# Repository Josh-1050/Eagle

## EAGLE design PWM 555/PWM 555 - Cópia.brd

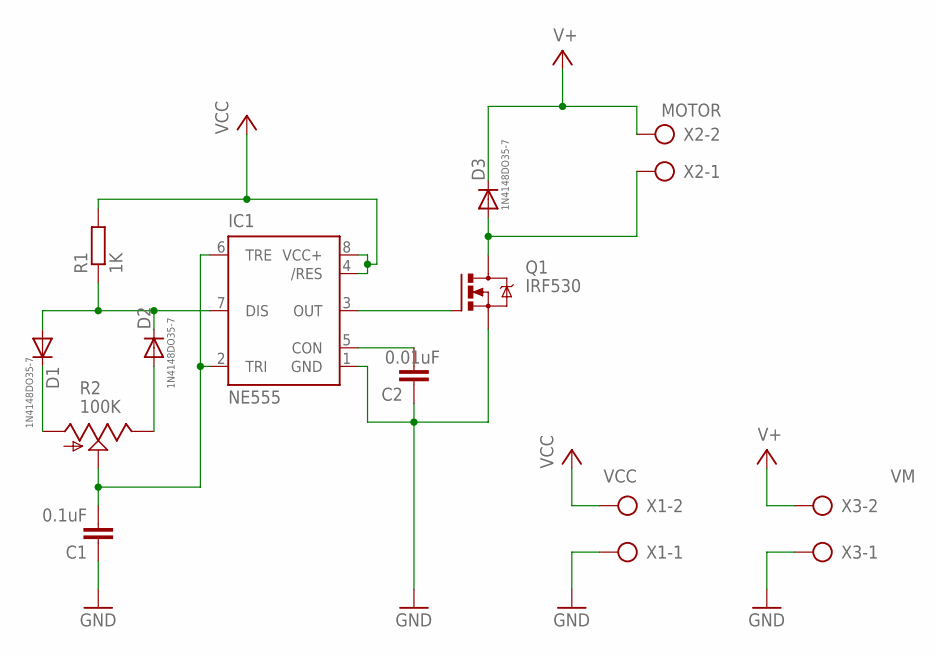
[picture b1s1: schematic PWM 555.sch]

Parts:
C1: 0.1uF; C025-024X044
C2: 0.01uF; C025-024X044
D1, D2, D3: 1N4148DO35-7; DO35-7
IC1: NE555; DIL-08
Q1: IRF530; TO220BV
R1: 1K; 0207/7
R2: 100K; S63S
X1: VCC; AK500/2-H
X2: MOTOR; AK500/2-H
X3: VM; AK500/2-H

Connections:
GND: C1.1, C2.1, IC1.1 (GND), Q1.S, X1.1, X3.1
unnamed: D1.A, D2.C, IC1.7 (DIS), R1.1
unnamed: C1.2, IC1.2 (TRI), IC1.6 (TRE), R2.S
unnamed: D1.C, R2.A
unnamed: D2.A, R2.E
unnamed: IC1.3 (OUT), Q1.G
unnamed: C2.2, IC1.5 (CON)
unnamed: D3.A, Q1.D, X2.1
V+: D3.C, X2.2, X3.2
VCC: IC1.4 (/RES), IC1.8 (VCC+), R1.2, X1.2

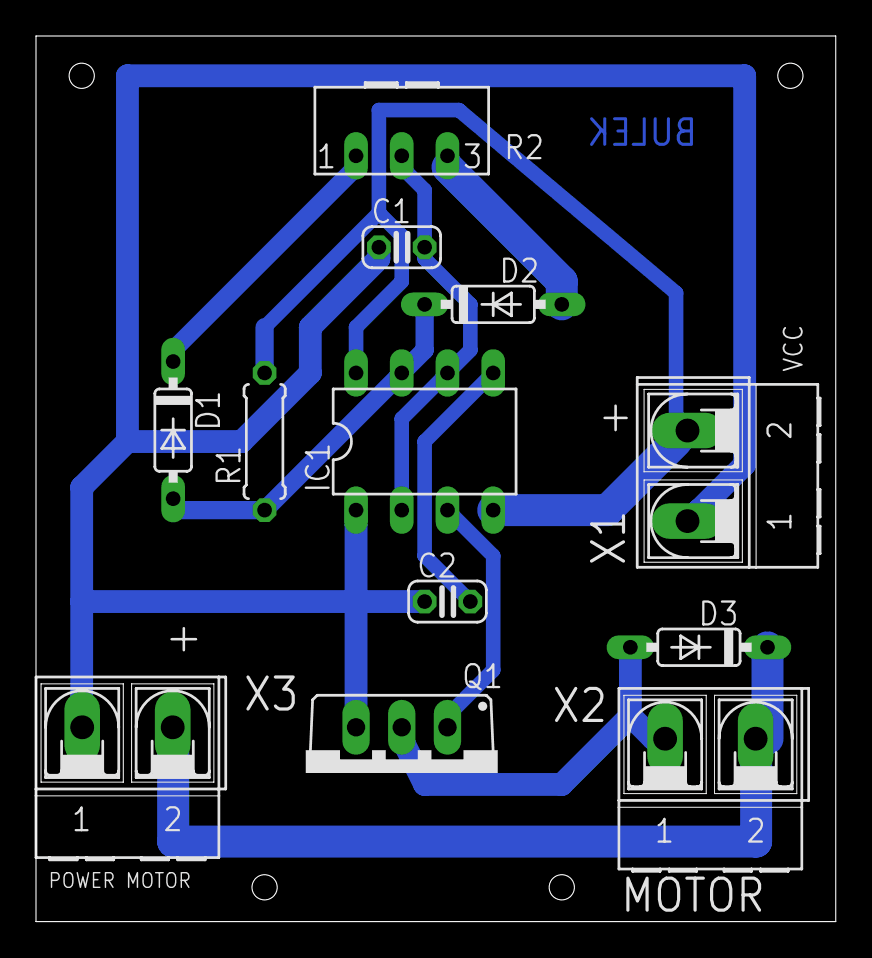
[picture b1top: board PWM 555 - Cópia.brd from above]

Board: 2 copper layers, 44.4 x 49.2 mm, 12 parts (0 on the bottom side), 10 nets.

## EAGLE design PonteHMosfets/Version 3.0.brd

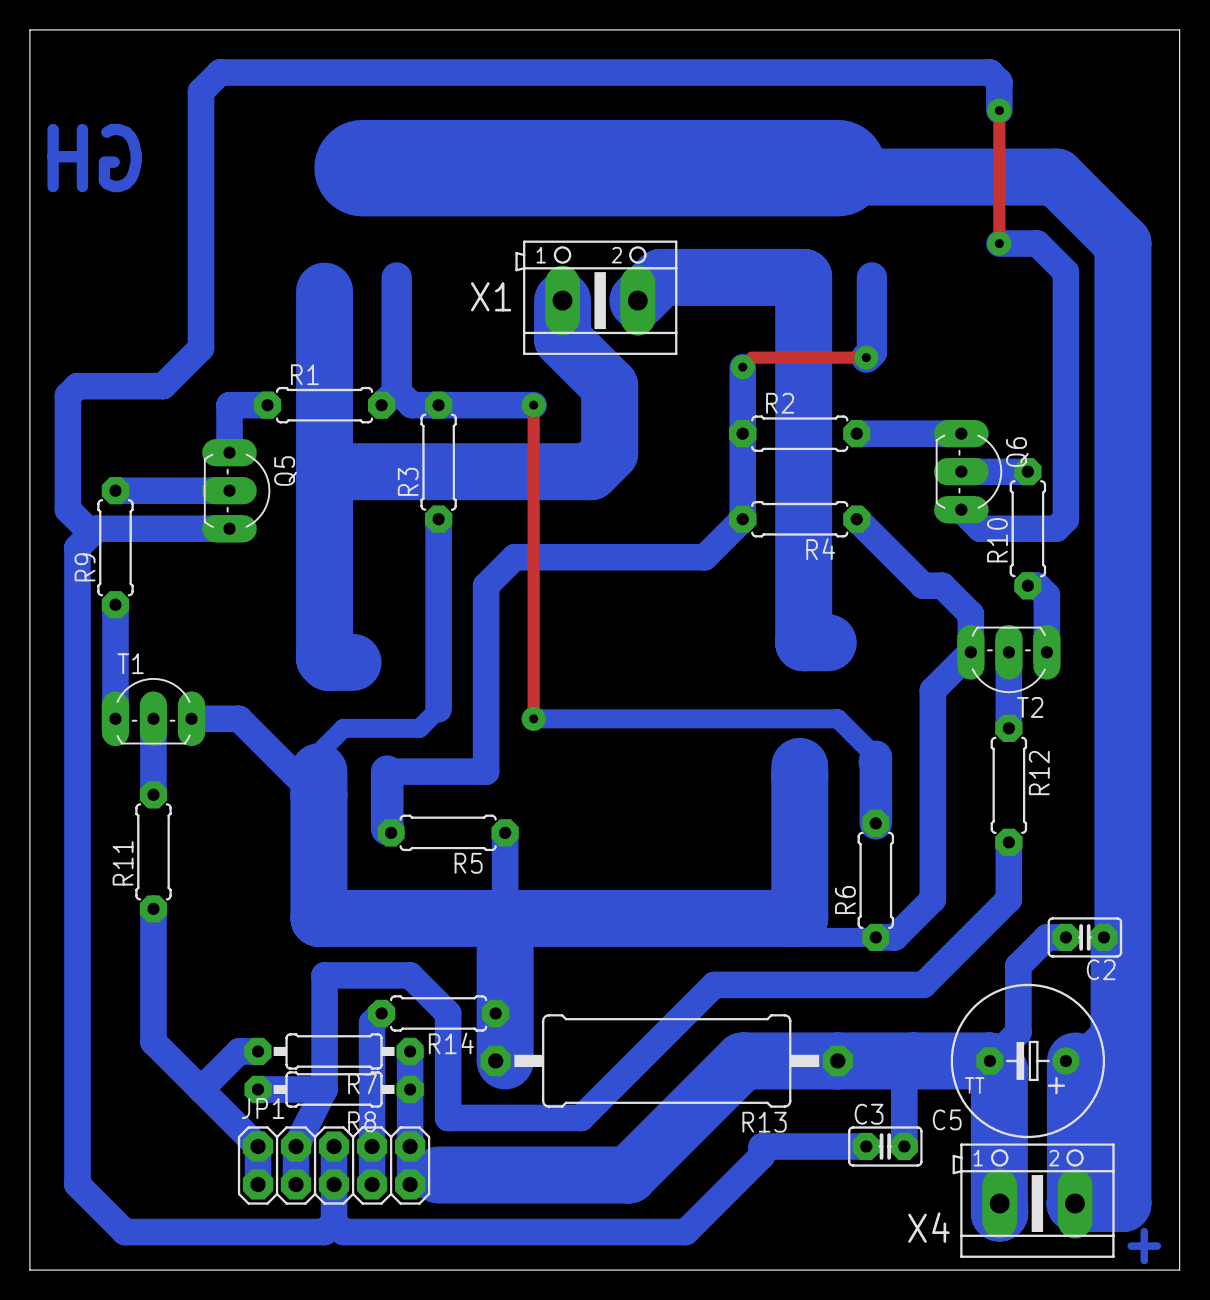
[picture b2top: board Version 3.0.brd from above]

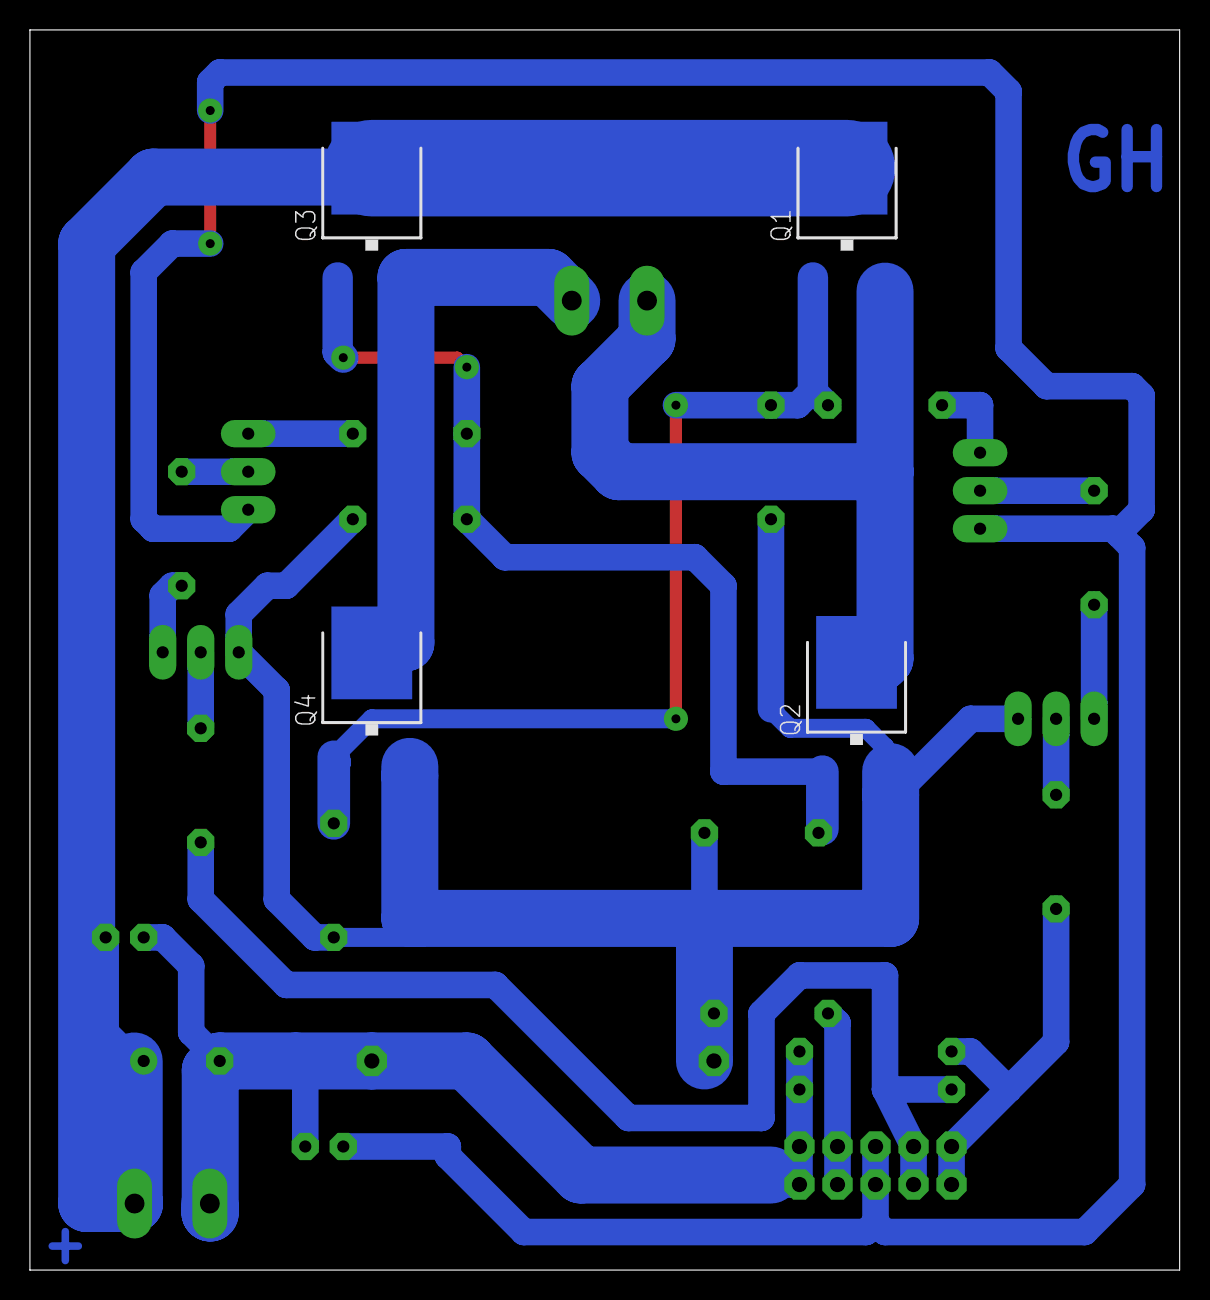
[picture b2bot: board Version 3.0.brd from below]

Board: 2 copper layers, 76.8 x 82.9 mm, 28 parts (4 on the bottom side), 19 nets.

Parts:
C2, C3: 100nf; C025-025X050
C5: 1000 uf; TT5D10
JP1: 2X05
Q1, Q2, Q3, Q4: PO903BDGTO252; TO252
Q5, Q6: BC557; TO92-EBC
R1, R2: 100R; 0207/7
R3, R4, R5, R6, R9, R10: 10k; 0207/7
R7, R8: 10k; 0207/10
R11, R12: 1k; 0207/7
R13: 0.33; 0617/22
R14: 4K7; 0207/7
T1, T2: BC547; TO92-CBE
X1, X4: AK500/2

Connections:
+12V: C2.1, C5.+, Q1.3, Q3.3, X4.2
+18V: C3.1, JP1.5, JP1.6, Q5.E, Q6.E
A: JP1.1, JP1.2, R7.2, R11.1
B: JP1.3, JP1.4, R8.2, R12.2
GND: C2.2, C3.2, C5.-, JP1.9, JP1.10, R7.1, R8.1, R13.1, X4.1
unnamed: Q1.1, Q4.1, R1.2, R3.2, R6.2
unnamed: Q2.1, Q3.1, R2.1, R4.2, R5.2
unnamed: Q1.2, Q2.3, X1.1
unnamed: Q3.2, Q4.3, X1.2
unnamed: Q6.C, R2.2
unnamed: Q5.C, R1.1
unnamed: Q5.B, R9.2
unnamed: R9.1, T1.C
unnamed: Q6.B, R10.2
unnamed: Q2.2, Q4.2, R3.1, R4.1, R5.1, R6.1, R13.2, R14.1, T1.E, T2.E
unnamed: R10.1, T2.C
unnamed: R11.2, T1.B
unnamed: R12.1, T2.B
SENSEA: JP1.7, JP1.8, R14.2

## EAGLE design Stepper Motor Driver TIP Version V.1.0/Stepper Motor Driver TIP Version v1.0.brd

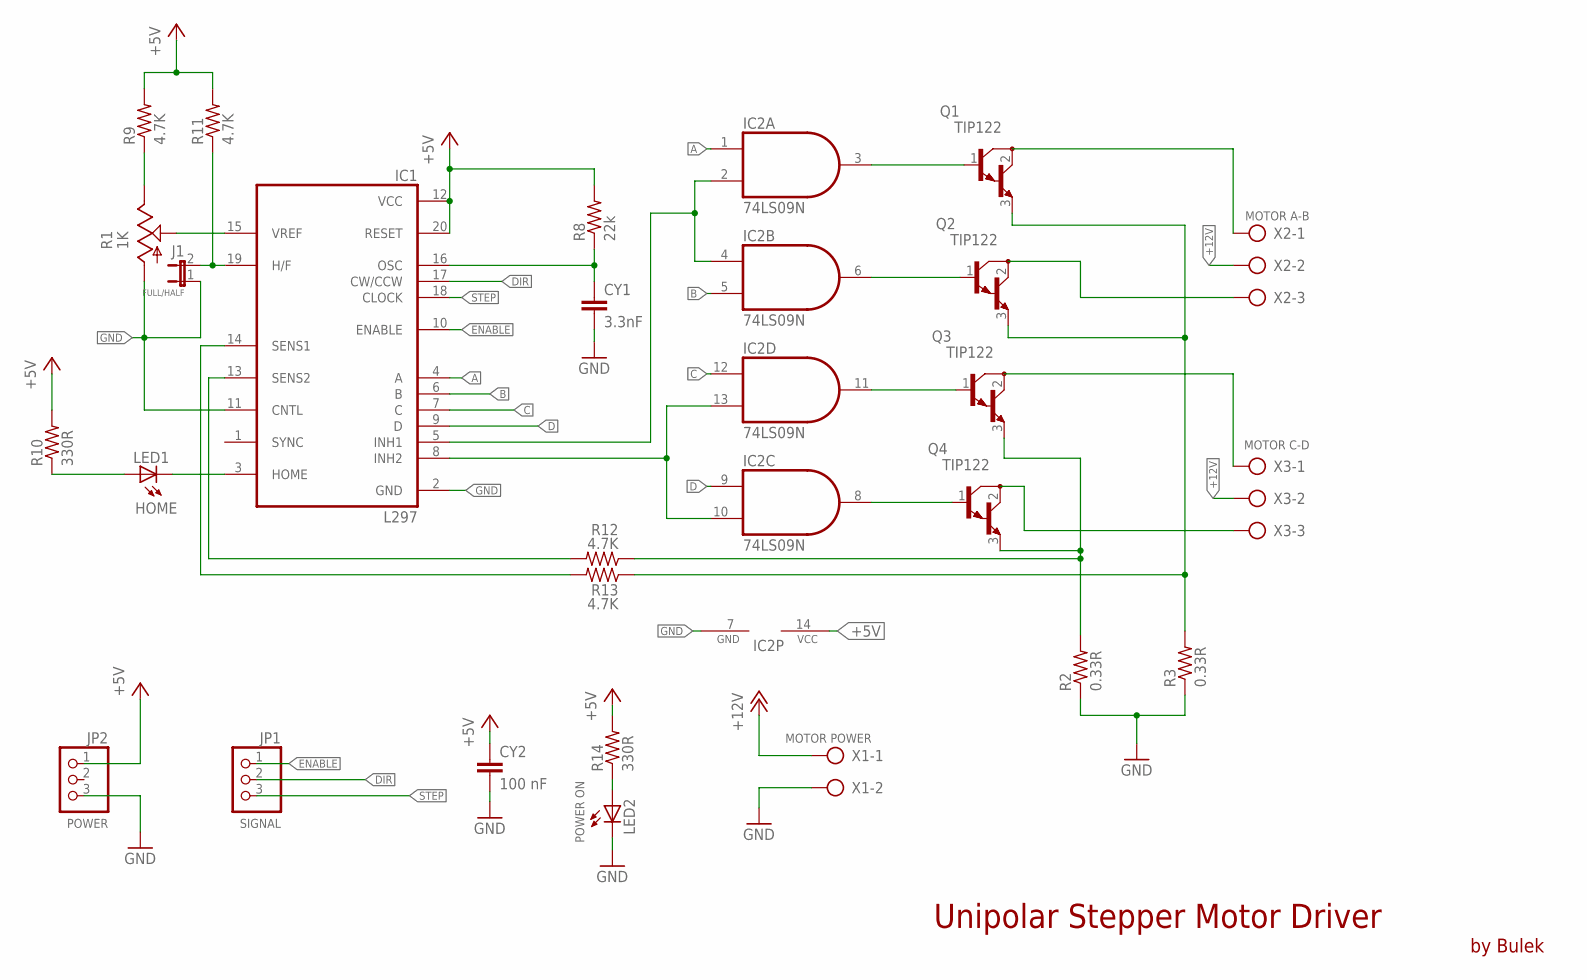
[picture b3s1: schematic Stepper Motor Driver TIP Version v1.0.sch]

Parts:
CY1: 3.3nF; YC7B5
CY2: 100 nF; YC7B5
FULL/HALF: J1; JP1
IC1: L297; DIL20
IC2: 74LS09N; DIL14
JP1: SIGNAL; 1X03/90
JP2: POWER; 1X03/90
LED1: HOME; LED5MM
LED2: POWER ON; LED5MM
Q1, Q2, Q3, Q4: TIP122; TO220V
R1: 1K; S63X
R2, R3: 0.33R; 0617/22
R8: 22k; 0207/10
R9, R11, R12, R13: 4.7K; 0207/10
R10, R14: 330R; 0207/10
X1: MOTOR POWER; AK300/2
X2: MOTOR A-B; AK300/3
X3: MOTOR C-D; AK300/3

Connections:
+5V: CY2.1, IC1.12 (VCC), IC1.20 (RESET), IC2.14 (VCC), JP2.1, R8.2, R9.2, R10.2, R11.2, R14.2
+12V: X1.1, X2.2, X3.2
A: IC1.4 (A), IC2.1 (I0)
B: IC1.6 (B), IC2.5 (I1)
C: IC1.7 (C), IC2.12 (I0)
D: IC1.9 (D), IC2.9 (I0)
DIR: IC1.17 (CW/CCW), JP1.2
ENABLE: IC1.10 (ENABLE), JP1.1
GND: CY1.2, CY2.2, FULL/HALF.1, IC1.2 (GND), IC1.11 (CNTL), IC2.7 (GND), JP2.3, LED2.K (C), R1.A, R2.1, R3.1, X1.2
INH1: IC1.5 (INH1), IC2.2 (I1), IC2.4 (I0)
INH2: IC1.8 (INH2), IC2.10 (I1), IC2.13 (I1)
unnamed: R1.E, R9.1
unnamed: IC1.15 (VREF), R1.S
unnamed: CY1.1, IC1.16 (OSC), R8.1
unnamed: IC1.3 (HOME), LED1.K (C)
unnamed: LED1.A, R10.1
unnamed: FULL/HALF.2, IC1.19 (H/F), R11.1
unnamed: IC1.14 (SENS1), R13.2
unnamed: IC1.13 (SENS2), R12.2
unnamed: IC2.8 (O), Q4.1 (B)
unnamed: IC2.11 (O), Q3.1 (B)
unnamed: IC2.6 (O), Q2.1 (B)
unnamed: IC2.3 (O), Q1.1 (B)
unnamed: Q1.3 (E), Q2.3 (E), R3.2, R13.1
unnamed: Q3.3 (E), Q4.3 (E), R2.2, R12.1
unnamed: Q1.2 (C), X2.1
unnamed: Q2.2 (C), X2.3
unnamed: Q3.2 (C), X3.1
unnamed: Q4.2 (C), X3.3
unnamed: LED2.A, R14.1
STEP: IC1.18 (CLOCK), JP1.3

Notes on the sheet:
Unipolar Stepper Motor Driver
by Bulek

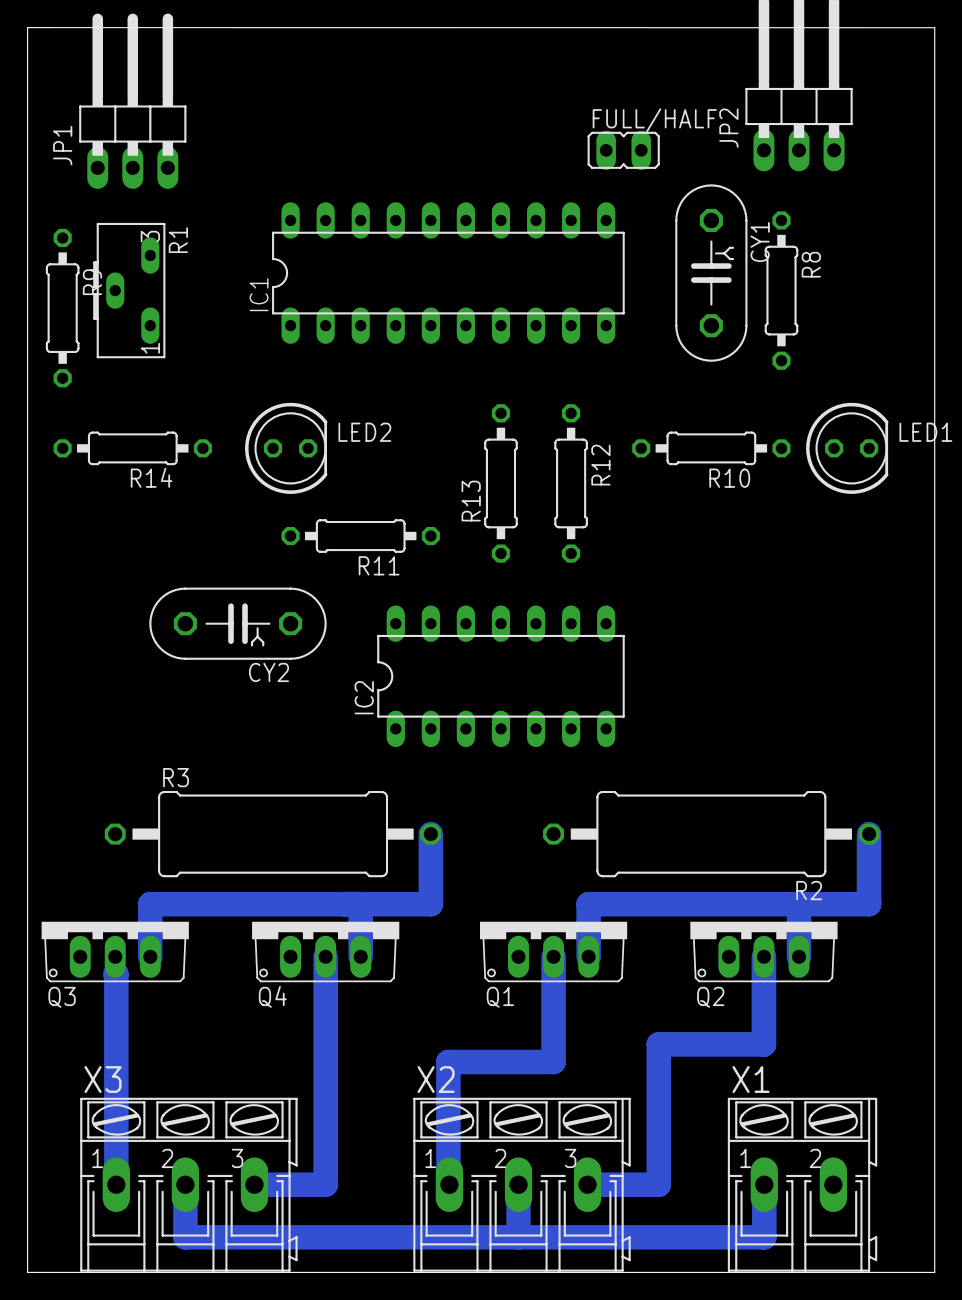
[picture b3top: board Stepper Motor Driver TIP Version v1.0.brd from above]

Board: 2 copper layers, 65.7 x 90.2 mm, 26 parts (0 on the bottom side), 31 nets.
